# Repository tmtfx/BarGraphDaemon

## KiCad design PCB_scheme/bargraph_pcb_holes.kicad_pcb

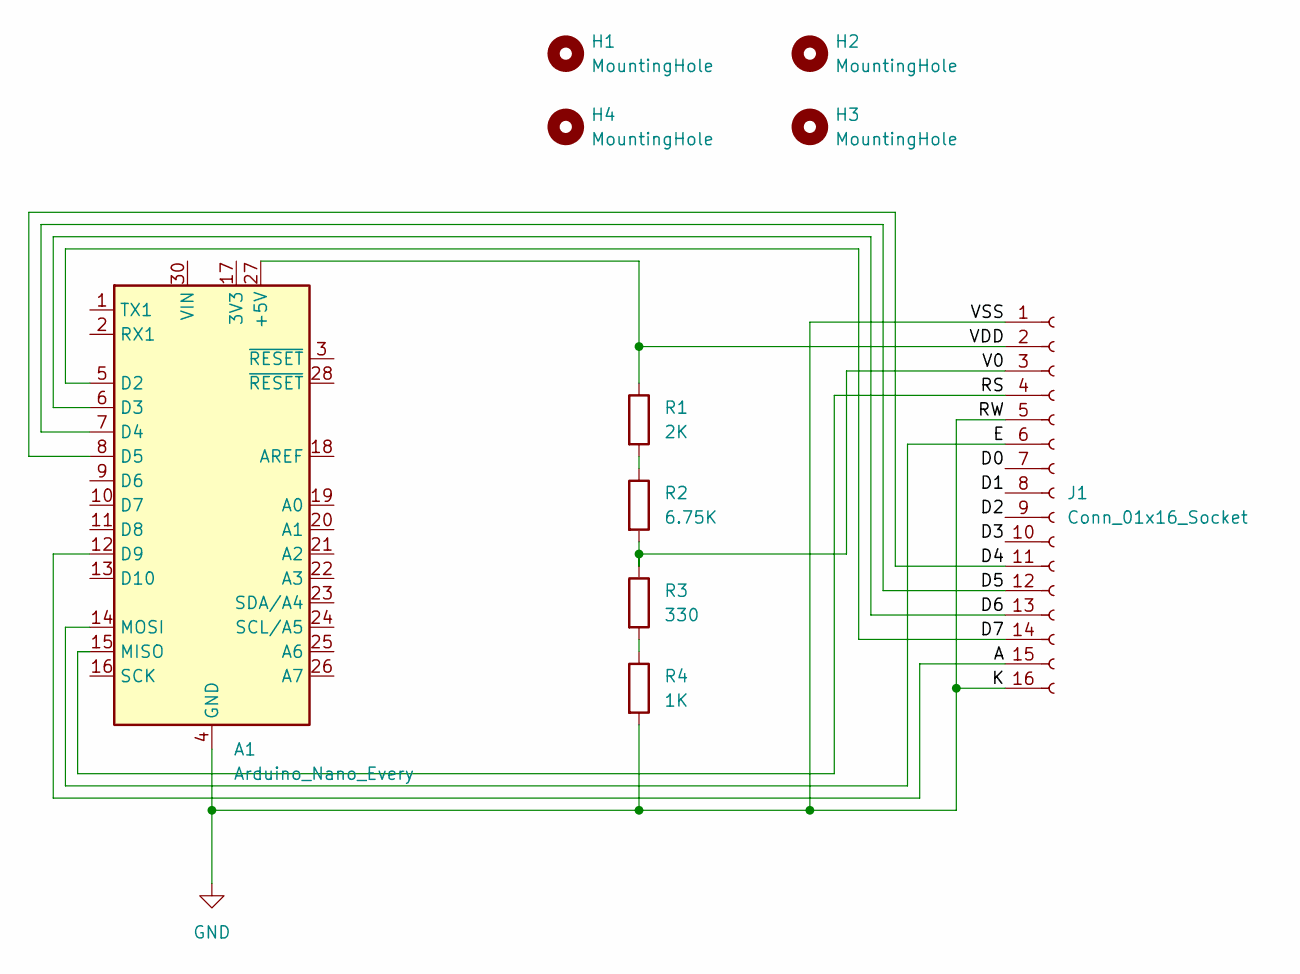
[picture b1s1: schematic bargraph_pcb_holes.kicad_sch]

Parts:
A1: Arduino_Nano_Every; Arduino_Nano
H1, H2, H3, H4: MountingHole; MountingHole_3.7mm
J1: Conn_01x16_Socket; PinHeader_1x16_P2.54mm_Vertical
R1: 2K; R_Axial_DIN0207_L6.3mm_D2.5mm_P5.08mm_Vertical
R2: 6.75K; R_Axial_DIN0207_L6.3mm_D2.5mm_P5.08mm_Vertical
R3: 330; R_Axial_DIN0207_L6.3mm_D2.5mm_P5.08mm_Vertical
R4: 1K; R_Axial_DIN0207_L6.3mm_D2.5mm_P5.08mm_Vertical

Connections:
/A: A1.12 (D9), J1.15
/D0: J1.7
/D1: J1.8
/D2: J1.9
/D3: J1.10
/D4: A1.8 (D5), J1.11
/D5: A1.7 (D4), J1.12
/D6: A1.6 (D3), J1.13
/D7: A1.5 (D2), J1.14
/E: A1.14 (MOSI), J1.6
/RS: A1.15 (MISO), J1.4
/V0: J1.3, R2.2, R3.1
/VDD: A1.27 (+5V), J1.2, R1.1
GND: A1.4 (GND), A1.29 (GND), J1.1, J1.5, J1.16, R4.2
unnamed: R1.2, R2.1
unnamed: R3.2, R4.1

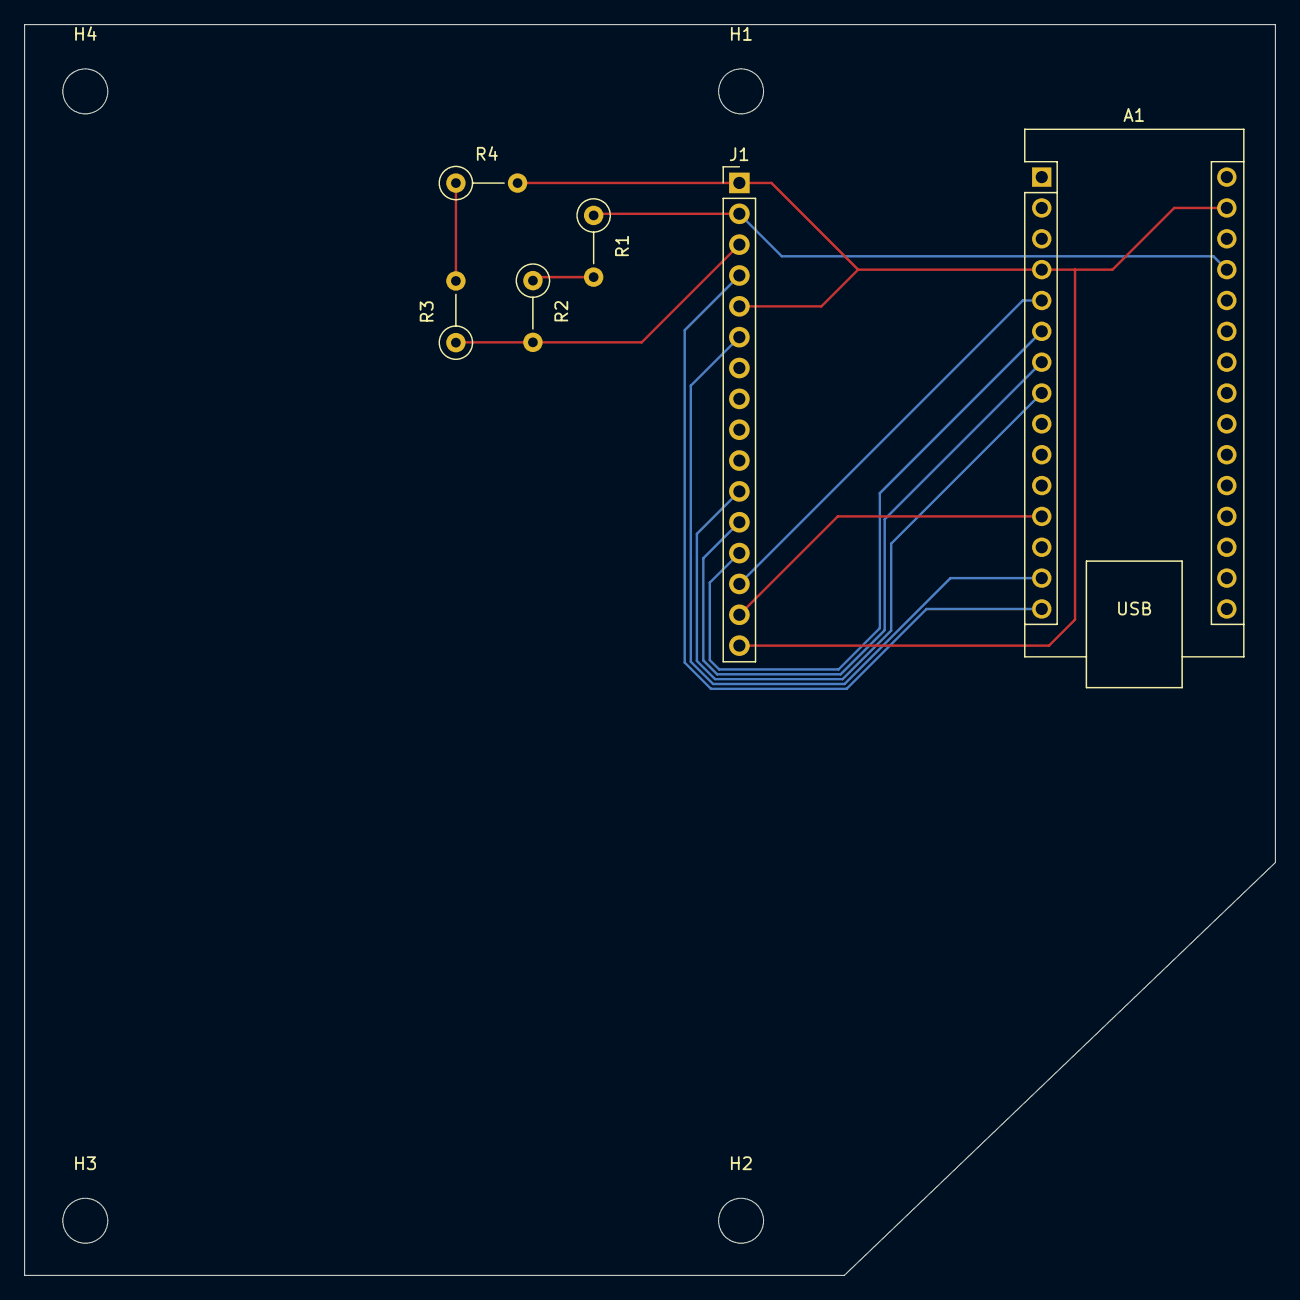
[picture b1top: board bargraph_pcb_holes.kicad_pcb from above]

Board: 2 copper layers, 103.0 x 103.0 mm, 10 parts (0 on the bottom side), 12 nets.

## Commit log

2024-11-14 primo commit
2024-11-15 Fix less bar shown and config file position
2024-11-15 fix vari su configurazione di più barre
2024-11-15 remove additional snooze
2024-11-16 Quit message
2024-11-16 add LICENSE and arduino source code
2024-11-16 move arduino sketch to the correct position
2024-11-16 add genio project config
2024-11-16 initial integration of remote commands
2024-11-17 add brightness to config
2024-11-17 fix brightness saving
2024-11-17 add remote shutdown
2024-11-17 test to reduce flickering
2024-11-17 fix message findstring, print debug message
2024-11-18 remove stdout for serial output
2024-11-18 set initial brightness
2024-11-18 configure labels and clear display
2024-11-18 command to clear lcd, fix less than 4 bars config
2024-11-18 Set and save serial path change
2024-11-19 avoid int8
2024-11-19 fix first toggle labels
2024-11-19 set Exclusive and background, change icon
2024-11-19 add Resources.rdef
2024-11-20 implement single value fullscreen graphic
2024-11-21 fix fullscreen graph
2024-11-21 single value graphic chart & fixes
2024-11-21 Fix for Haiku 32bit
2024-11-28 Add PCB
